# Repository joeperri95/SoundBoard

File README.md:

# Soundboard

wav audio player

## Rev 2.0 changes

- Add IMU
- Add microSD card
- Use dedicated heaphone amp
- Use I2S DAC 
- Add SDRAM
- Changed to stm32f429
- Fix flash pins

### TODO Rev 2.0
- determine how to do buttons
- create BOM
- layout

## Rev 1.0 changes

- Went exlusively with JLCPCB parts and paid for assembly service
- Removed lipo circuitry, sd card and hall effect sensor
- Added spi flash to store music
- Removed FTDI went for a direct USB connection to the STM32
- Changed to a smaller stm32f405
- Reworked output stage to include a digital potentiometer
- Significantly reduced size of board
- Went to a 4 layer pcb

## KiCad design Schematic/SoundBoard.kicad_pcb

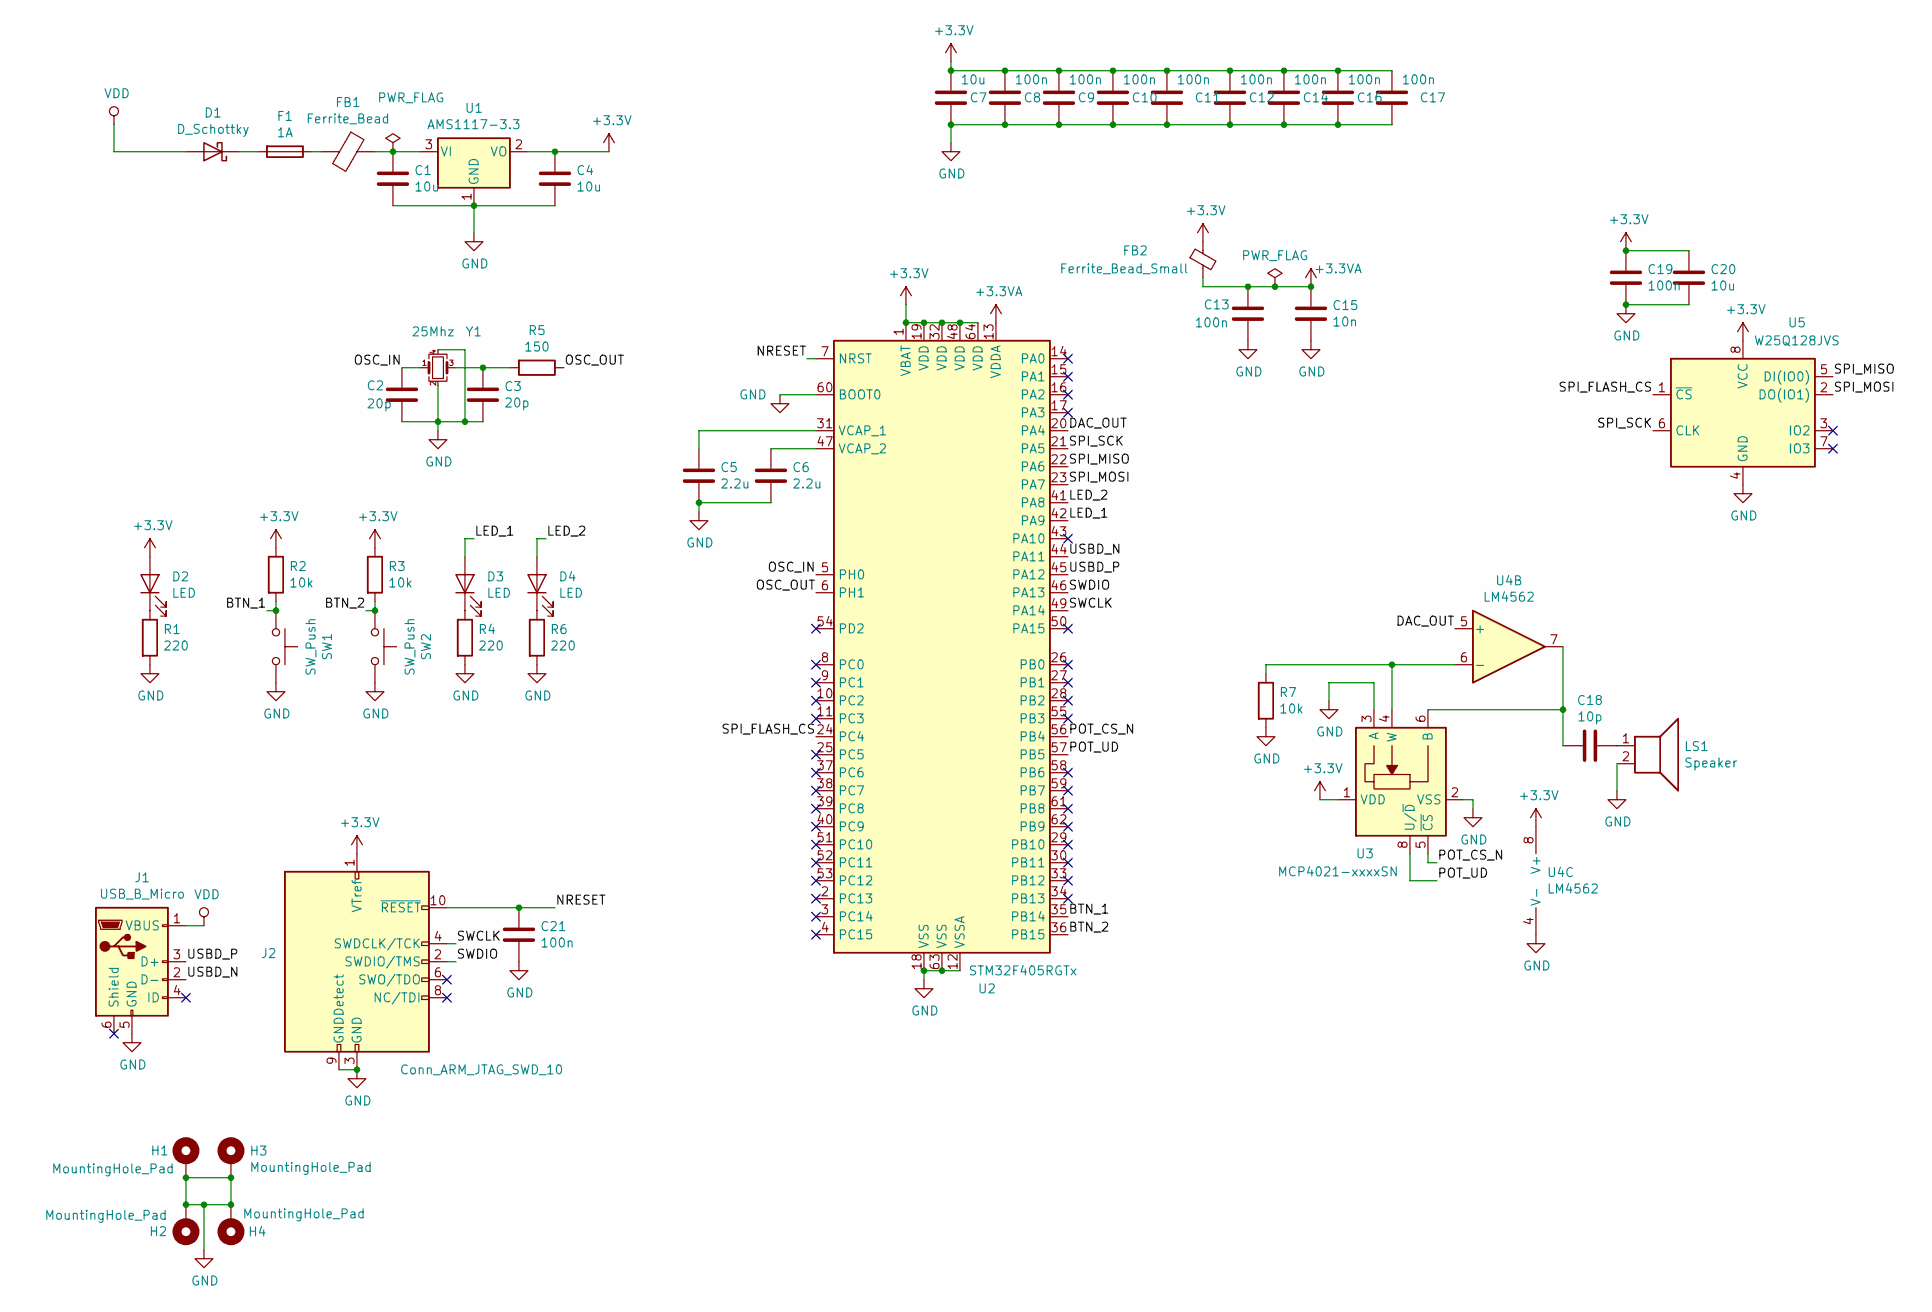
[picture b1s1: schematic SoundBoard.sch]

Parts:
C1, C4, C7, C20: 10u; C_0603_1608Metric
C2, C3: 20p; C_0402_1005Metric
C5, C6: 2.2u; C_0603_1608Metric
C8, C9, C10, C11, C12, C13, C14, C16, C17, C19, C21: 100n; C_0402_1005Metric
C15: 10n; C_0402_1005Metric
C18: 10p; C_0805_2012Metric
D1: D_Schottky; D_SOD-123
D2, D3, D4: LED; LED_0603_1608Metric
F1: 1A; Fuse_0603_1608Metric
FB1: Ferrite_Bead; L_0805_2012Metric
FB2: Ferrite_Bead_Small; L_0805_2012Metric
H1, H2, H3, H4: MountingHole_Pad; MountingHole_4.3mm_M4_Pad
J1: USB_B_Micro; USB_Micro-B_Amphenol_10103594-0001LF_Horizontal
J2: Conn_ARM_JTAG_SWD_10; PinHeader_2x05_P1.27mm_Vertical_SMD
LS1: Speaker; speaker_pads
R1, R4, R6: 220; R_0603_1608Metric
R2, R3, R7: 10k; R_0603_1608Metric
R5: 150; R_0402_1005Metric
SW1, SW2: SW_Push; SW_Push_1P1T_NO_6x6mm_H9.5mm
U1: AMS1117-3.3; SOT-223-3_TabPin2
U2: STM32F405RGTx; LQFP-64_10x10mm_P0.5mm
U3: MCP4021-xxxxSN; SOIC-8_3.9x4.9mm_P1.27mm
U4: LM4562; SOIC-8_3.9x4.9mm_P1.27mm
U5: W25Q128JVS; SOIC-8_5.23x5.23mm_P1.27mm
Y1: 25Mhz; Crystal_SMD_3225-4Pin_3.2x2.5mm

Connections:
+3.3VA: C13.1, C15.1, FB2.2, U2.13 (VDDA)
+3V3: C4.1, C7.1, C8.1, C9.1, C10.1, C11.1, C12.1, C14.1, C16.1, C17.1, C19.1, C20.1, D2.2 (A), FB2.1, J2.1 (VTref), R2.1, R3.1, U1.2 (VO), U2.1 (VBAT), U2.19 (VDD), U2.32 (VDD), U2.48 (VDD), U2.64 (VDD), U3.1 (VDD), U4.8 (V+), U5.8 (VCC)
/BTN_1: R2.2, SW1.1, U2.35 (PB14)
/BTN_2: R3.2, SW2.1, U2.36 (PB15)
/DAC_OUT: U2.20 (PA4), U4.5 (+)
/LED_1: D3.2 (A), U2.42 (PA9)
/LED_2: D4.2 (A), U2.41 (PA8)
/NRESET: C21.1, J2.10 (~RESET~), U2.7 (NRST)
/OSC_IN: C2.1, U2.5 (PH0), Y1.1
/OSC_OUT: R5.1, U2.6 (PH1)
/POT_CS_N: U2.56 (PB4), U3.5 (~CS)
/POT_UD: U2.57 (PB5), U3.8 (U/~D)
/SPI_FLASH_CS: U2.24 (PC4), U5.1 (~CS)
/SPI_MISO: U2.22 (PA6), U5.5 (DI(IO0))
/SPI_MOSI: U2.23 (PA7), U5.2 (DO(IO1))
/SPI_SCK: U2.21 (PA5), U5.6 (CLK)
/SWCLK: J2.4 (SWDCLK/TCK), U2.49 (PA14)
/SWDIO: J2.2 (SWDIO/TMS), U2.46 (PA13)
/USBD_N: J1.2 (D-), U2.44 (PA11)
/USBD_P: J1.3 (D+), U2.45 (PA12)
GND: C1.2, C2.2, C3.2, C4.2, C5.2, C6.2, C7.2, C8.2, C9.2, C10.2, C11.2, C12.2, C13.2, C14.2, C15.2, C16.2, C17.2, C19.2, C20.2, C21.2, H1.1, H2.1, H3.1, H4.1, J1.5 (GND), J2.3 (GND), J2.5 (GND), J2.9 (GNDDetect), LS1.2, R1.2, R4.2, R6.2, R7.2, SW1.2, SW2.2, U1.1 (GND), U2.12 (VSSA), U2.18 (VSS), U2.60 (BOOT0), U2.63 (VSS), U3.2 (VSS), U3.3 (A), U4.4 (V-), U5.4 (GND), Y1.2, Y1.4
unnamed: C1.1, FB1.1, U1.3 (VI)
unnamed: C3.1, R5.2, Y1.3
unnamed: C5.1, U2.31 (VCAP_1)
unnamed: C6.1, U2.47 (VCAP_2)
unnamed: C18.1, LS1.1
unnamed: C18.2, U3.6 (B), U4.7
unnamed: D1.1 (K), F1.2
unnamed: D2.1 (K), R1.1
unnamed: D3.1 (K), R4.1
unnamed: D4.1 (K), R6.1
unnamed: F1.1, FB1.2
unnamed: R7.1, U3.4 (W), U4.6 (-)
VDD: D1.2 (A), J1.1 (VBUS)

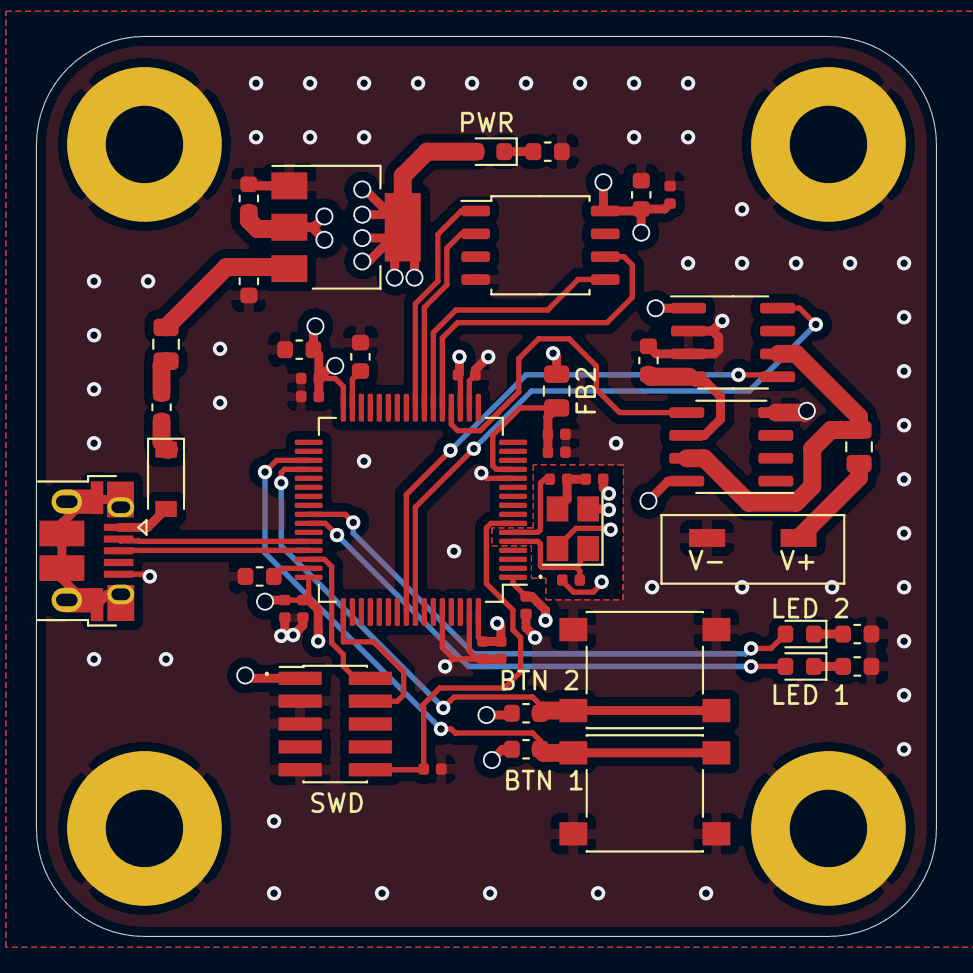
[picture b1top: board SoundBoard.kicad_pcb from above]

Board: 4 copper layers, 50.0 x 50.0 mm, 50 parts (0 on the bottom side), 34 nets.

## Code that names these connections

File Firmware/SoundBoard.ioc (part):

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Mcu.Name=STM32F405RGTx
Mcu.Package=LQFP64
Mcu.UserName=STM32F405RGTx
PA11.Mode=Device_Only
PA11.Signal=USB_OTG_FS_DM
PA12.Mode=Device_Only
PA12.Signal=USB_OTG_FS_DP
PA13.Signal=SYS_JTMS-SWDIO
PA14.Signal=SYS_JTCK-SWCLK
PA4.Signal=GPIO_Output
PA5.GPIOParameters=GPIO_Label
PA5.GPIO_Label=SPI_SCK
PA5.Signal=GPIO_Output
PA6.GPIOParameters=GPIO_Label
PA6.GPIO_Label=SPI_MOSI
PA6.Signal=GPIO_Output
PA7.GPIOParameters=GPIO_Label
PA7.GPIO_Label=SPI_MISO
PA7.Signal=GPIO_Input
PA8.GPIOParameters=GPIO_Label
PA8.GPIO_Label=LED_2
PA8.Signal=GPIO_Output
PA9.GPIOParameters=GPIO_Label
PA9.GPIO_Label=LED_1
PA9.Signal=GPIO_Output
PB14.GPIOParameters=GPIO_Label
PB14.GPIO_Label=BTN_1
PB14.Signal=GPIO_Input
PB15.GPIOParameters=GPIO_Label
PB15.GPIO_Label=BTN_2
PB15.Signal=GPIO_Input
PB4.GPIOParameters=GPIO_Label
PB4.GPIO_Label=POT_CS_N
PB4.Signal=GPIO_Output
PB5.GPIOParameters=GPIO_Label
PB5.GPIO_Label=POT_UD
PB5.Signal=GPIO_Output
PC4.GPIOParameters=GPIO_Label
PC4.GPIO_Label=SPI_FLASH_CS_N
PC4.Signal=GPIO_Output
PH0-OSC_IN.Mode=HSE-External-Oscillator
PH0-OSC_IN.Signal=RCC_OSC_IN
PH1-OSC_OUT.Mode=HSE-External-Oscillator
PH1-OSC_OUT.Signal=RCC_OSC_OUT
RCC.HSE_VALUE=25000000
RCC.SYSCLKFreq_VALUE=25000000
RCC.SYSCLKSource=RCC_SYSCLKSOURCE_HSE
board=custom

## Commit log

2020-01-20 Add Kicad project files with main ICs
2020-01-22 Add power circuitry
2020-01-23 Add passives
2020-01-24 Perform annotation start assigning footprints
2020-01-26 Selected components
2020-01-26 Add i2c pullups and start placement
2020-01-28 Preliminary routing
2020-02-04 Continue work on layout
2020-02-07 Complete layout
2020-02-09 Add gerbers
2020-02-21 Add BOM
2020-05-06 Inital rev 1.0 commit
2020-05-11 Footprint associations
2020-05-13 Perform layout
2020-05-13 Update gerbers
2020-05-13 Create BOM remove unnecessary files
2020-05-14 Modify manufacturing output per JLC
2020-06-16 Received rev 1 boards and performed initial testing
2020-07-13 Rev 1 manufacturing update
2020-07-14 Initial rev 2 commit
2020-08-04 Begin rev 2 part selection and schematic
2020-08-07 Rev 0 historical data
2020-08-10 Write GPIO driver
2020-08-18 Complete part selection. Start connections
2020-08-21 Complete connections except for display to be chosen
2020-09-10 Additional rework
2020-09-15 Choose display. Complete schematic
